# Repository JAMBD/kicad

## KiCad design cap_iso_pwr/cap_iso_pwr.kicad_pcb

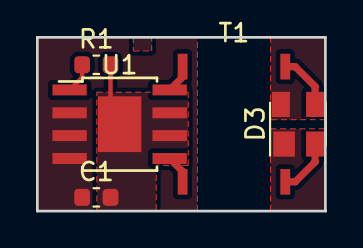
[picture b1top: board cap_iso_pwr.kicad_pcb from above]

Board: 2 copper layers, 16.0 x 9.7 mm, 6 parts (0 on the bottom side), 9 nets.

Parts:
C1: C_Small; C_0603_1608Metric
D3: D_Bridge_-AA+; SOT-143
J1: isolated_power_module; iso_power_module
R1: R_Small; R_0603_1608Metric
T1: transformer; 750316743
U1: MAX256ASA; TI_SO-PowerPAD-8

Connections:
unnamed: C1.1, J1.3, U1.2, U1.3, U1.4
unnamed: C1.2, J1.1, R1.2, U1.6, U1.7, U1.9
unnamed: D3.1, J1.7
unnamed: D3.2, T1.5
unnamed: D3.3, T1.4
unnamed: D3.4, J1.8
unnamed: R1.1, U1.1
unnamed: T1.1, U1.8
unnamed: T1.8, U1.5

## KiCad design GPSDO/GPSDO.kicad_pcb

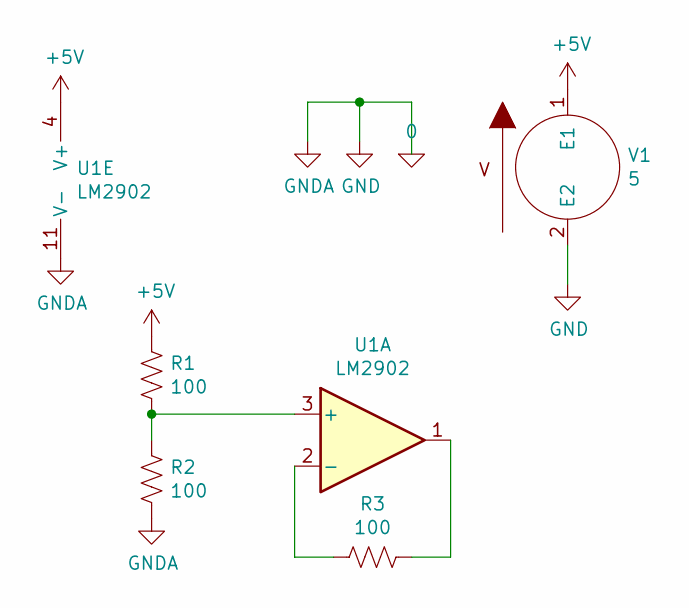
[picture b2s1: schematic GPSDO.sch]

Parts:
R1, R2, R3: 100; R_Axial_DIN0204_L3.6mm_D1.6mm_P1.90mm_Vertical
U1: LM2902; DIP-14_W7.62mm
V1: 5; SW_DIP_SPSTx10_Slide_6.7x26.96mm_W6.73mm_P2.54mm_LowProfile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

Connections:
0: R2.2, U1.11 (V-), V1.2 (E2)
+5V: R1.1, U1.4 (V+), V1.1 (E1)
unnamed: R1.2, R2.1, U1.3 (+)
unnamed: R3.1, U1.1
unnamed: R3.2, U1.2 (-)

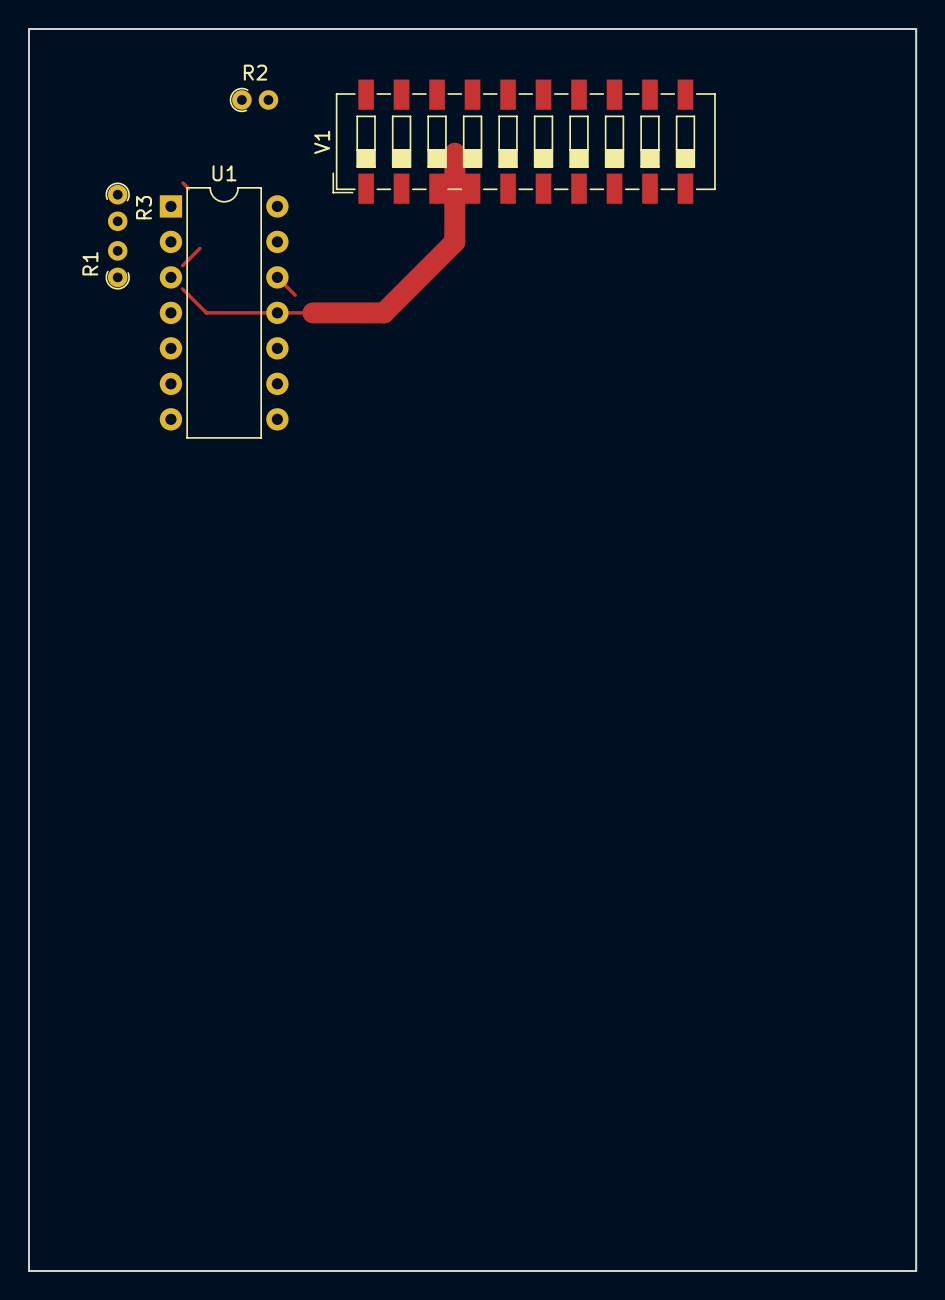
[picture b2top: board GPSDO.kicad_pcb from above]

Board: 2 copper layers, 63.5 x 88.9 mm, 5 parts (0 on the bottom side), 5 nets.

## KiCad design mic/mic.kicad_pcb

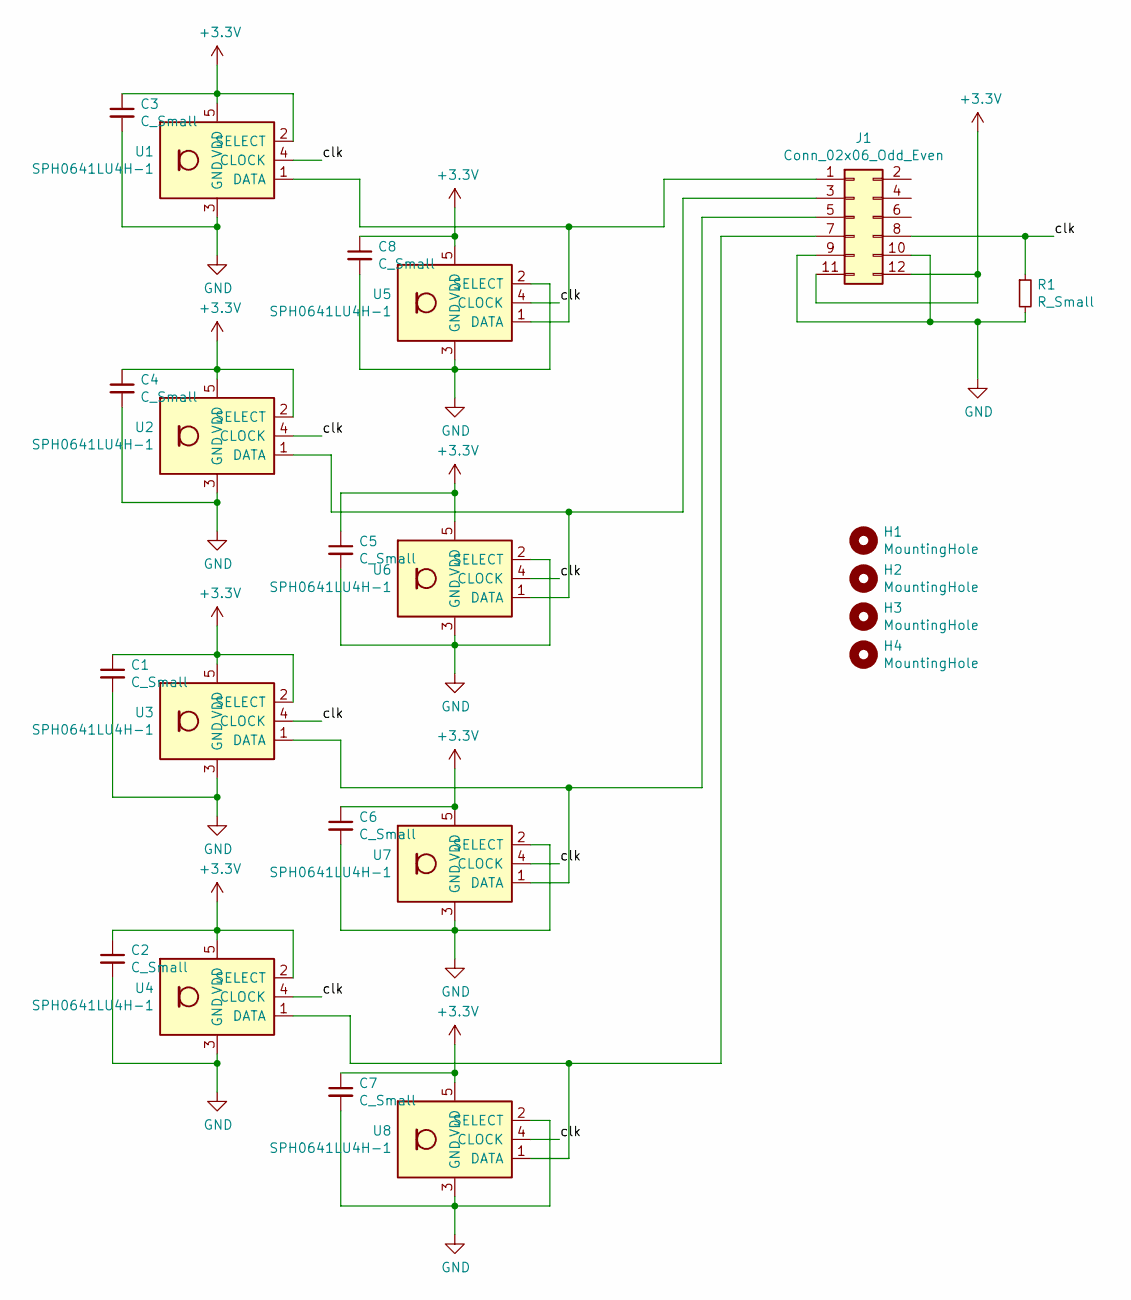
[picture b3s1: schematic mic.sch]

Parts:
C1, C2, C3, C4, C5, C6, C7, C8: C_Small; C_0603_1608Metric
H1, H2, H3, H4: MountingHole; MountingHole_3.2mm_M3
J1: Conn_02x06_Odd_Even; PinHeader_2x06_P2.54mm_Vertical
R1: R_Small; R_0603_1608Metric
U1, U2, U3, U4, U5, U6, U7, U8: SPH0641LU4H-1; KNOWLES_SPH0641LU4H-1

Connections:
+3V3: C1.1, C2.1, C3.1, C4.1, C5.1, C6.1, C7.1, C8.1, J1.11, J1.12, U1.2 (SELECT), U1.5 (VDD), U2.2 (SELECT), U2.5 (VDD), U3.2 (SELECT), U3.5 (VDD), U4.2 (SELECT), U4.5 (VDD), U5.5 (VDD), U6.5 (VDD), U7.5 (VDD), U8.5 (VDD)
/clk: J1.8, R1.1, U1.4 (CLOCK), U2.4 (CLOCK), U3.4 (CLOCK), U4.4 (CLOCK), U5.4 (CLOCK), U6.4 (CLOCK), U7.4 (CLOCK), U8.4 (CLOCK)
GND: C1.2, C2.2, C3.2, C4.2, C5.2, C6.2, C7.2, C8.2, J1.9, J1.10, R1.2, U1.3 (GND), U2.3 (GND), U3.3 (GND), U4.3 (GND), U5.2 (SELECT), U5.3 (GND), U6.2 (SELECT), U6.3 (GND), U7.2 (SELECT), U7.3 (GND), U8.2 (SELECT), U8.3 (GND)
unnamed: J1.1, U1.1 (DATA), U5.1 (DATA)
unnamed: J1.3, U2.1 (DATA), U6.1 (DATA)
unnamed: J1.5, U3.1 (DATA), U7.1 (DATA)
unnamed: J1.7, U4.1 (DATA), U8.1 (DATA)

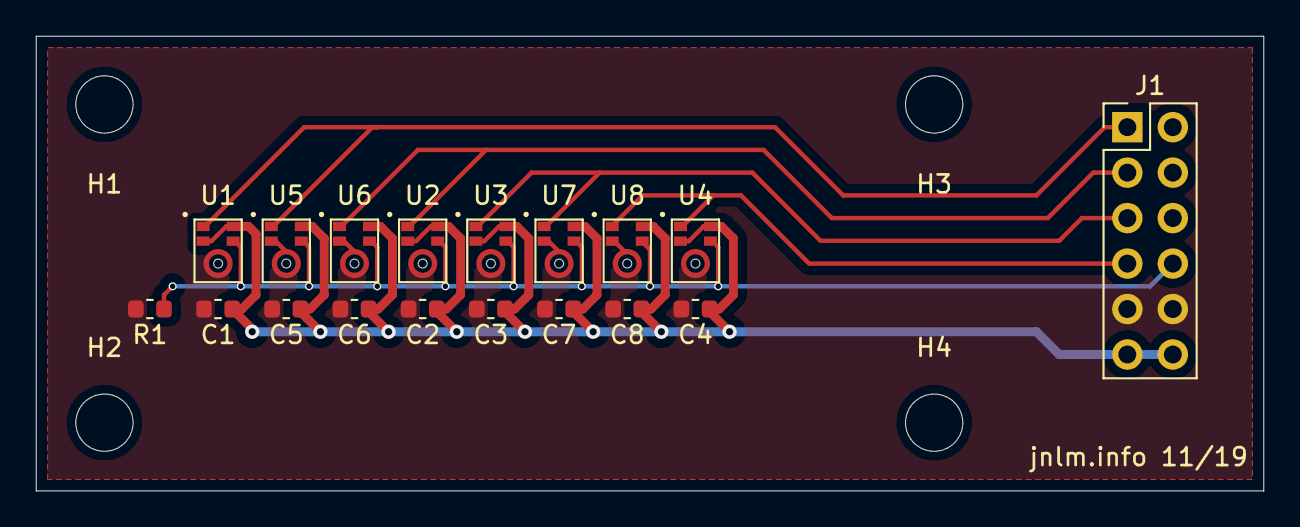
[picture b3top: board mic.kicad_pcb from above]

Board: 2 copper layers, 68.6 x 25.4 mm, 22 parts (0 on the bottom side), 7 nets.

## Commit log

2019-11-23 upload all the things
2020-02-01 Add more projects
2020-02-09 add pcb inductor
